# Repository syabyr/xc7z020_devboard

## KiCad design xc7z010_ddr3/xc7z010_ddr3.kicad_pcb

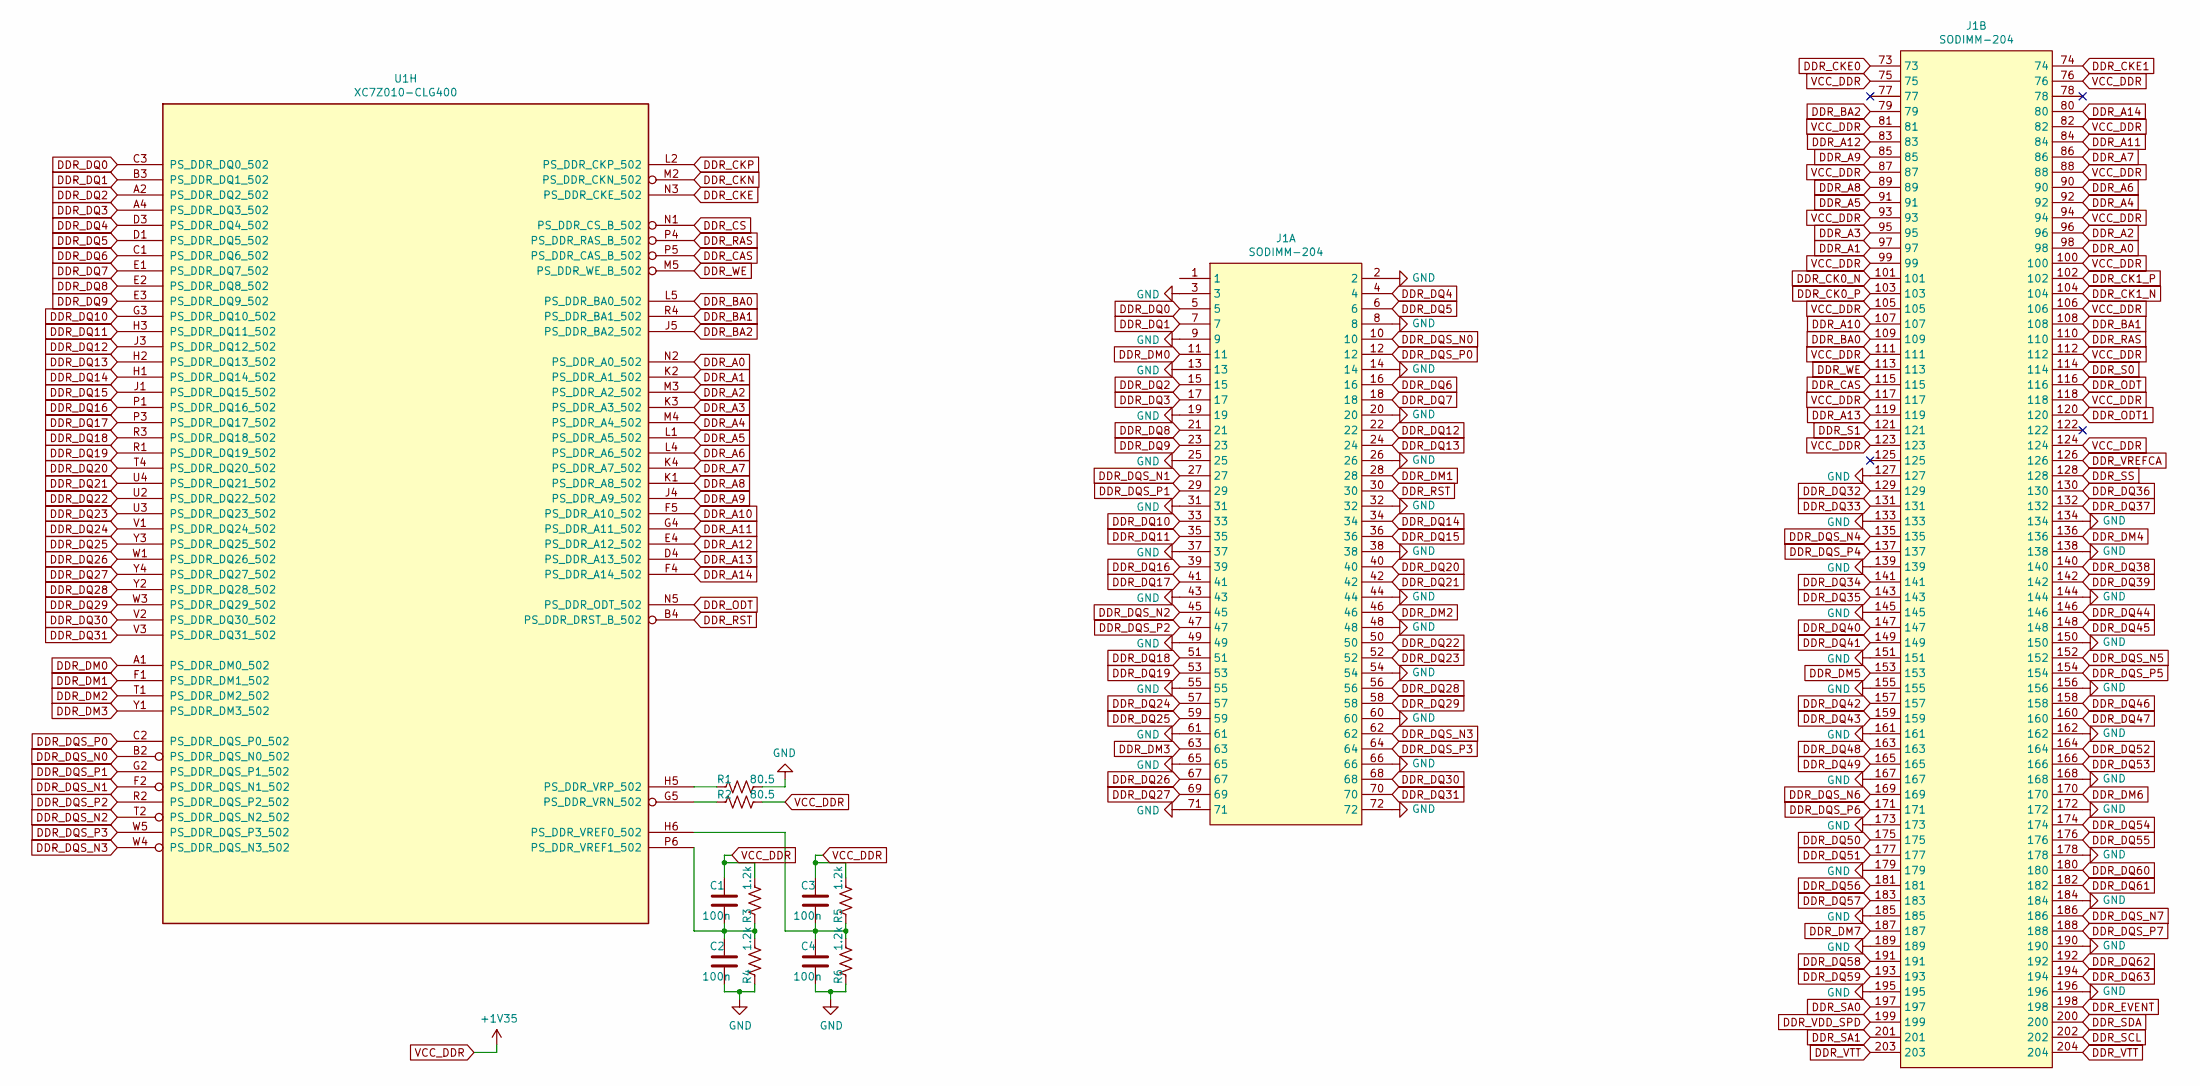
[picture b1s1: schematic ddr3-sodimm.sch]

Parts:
C1, C2, C3, C4: 100n; C_0402_1005Metric
J1: SODIMM-204; Socket_SODIMM_DDR3_TE_2013289_Debug
R1, R2: 80.5; R_0402_1005Metric
R3, R4, R5, R6: 1.2k; R_0402_1005Metric
U1: XC7Z010-CLG400; CLG400-0.8

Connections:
DDR_A0: J1.98, U1.N2 (PS_DDR_A0_502)
DDR_A1: J1.97, U1.K2 (PS_DDR_A1_502)
DDR_A2: J1.96, U1.M3 (PS_DDR_A2_502)
DDR_A3: J1.95, U1.K3 (PS_DDR_A3_502)
DDR_A4: J1.92, U1.M4 (PS_DDR_A4_502)
DDR_A5: J1.91, U1.L1 (PS_DDR_A5_502)
DDR_A6: J1.90, U1.L4 (PS_DDR_A6_502)
DDR_A7: J1.86, U1.K4 (PS_DDR_A7_502)
DDR_A8: J1.89, U1.K1 (PS_DDR_A8_502)
DDR_A9: J1.85, U1.J4 (PS_DDR_A9_502)
DDR_A10: J1.107, U1.F5 (PS_DDR_A10_502)
DDR_A11: J1.84, U1.G4 (PS_DDR_A11_502)
DDR_A12: J1.83, U1.E4 (PS_DDR_A12_502)
DDR_A13: J1.119, U1.D4 (PS_DDR_A13_502)
DDR_A14: J1.80, U1.F4 (PS_DDR_A14_502)
DDR_BA0: J1.109, U1.L5 (PS_DDR_BA0_502)
DDR_BA1: J1.108, U1.R4 (PS_DDR_BA1_502)
DDR_BA2: J1.79, U1.J5 (PS_DDR_BA2_502)
DDR_CAS: J1.115, U1.P5 (PS_DDR_CAS_B_502)
DDR_CK0_N: J1.101
DDR_CK0_P: J1.103
DDR_CK1_N: J1.104
DDR_CK1_P: J1.102
DDR_CKE: U1.N3 (PS_DDR_CKE_502)
DDR_CKE0: J1.73
DDR_CKE1: J1.74
DDR_CKN: U1.M2 (PS_DDR_CKN_502)
DDR_CKP: U1.L2 (PS_DDR_CKP_502)
DDR_CS: U1.N1 (PS_DDR_CS_B_502)
DDR_DM0: J1.11, U1.A1 (PS_DDR_DM0_502)
DDR_DM1: J1.28, U1.F1 (PS_DDR_DM1_502)
DDR_DM2: J1.46, U1.T1 (PS_DDR_DM2_502)
DDR_DM3: J1.63, U1.Y1 (PS_DDR_DM3_502)
DDR_DM4: J1.136
DDR_DM5: J1.153
DDR_DM6: J1.170
DDR_DM7: J1.187
DDR_DQ0: J1.5, U1.C3 (PS_DDR_DQ0_502)
DDR_DQ1: J1.7, U1.B3 (PS_DDR_DQ1_502)
DDR_DQ2: J1.15, U1.A2 (PS_DDR_DQ2_502)
DDR_DQ3: J1.17, U1.A4 (PS_DDR_DQ3_502)
DDR_DQ4: J1.4, U1.D3 (PS_DDR_DQ4_502)
DDR_DQ5: J1.6, U1.D1 (PS_DDR_DQ5_502)
DDR_DQ6: J1.16, U1.C1 (PS_DDR_DQ6_502)
DDR_DQ7: J1.18, U1.E1 (PS_DDR_DQ7_502)
DDR_DQ8: J1.21, U1.E2 (PS_DDR_DQ8_502)
DDR_DQ9: J1.23, U1.E3 (PS_DDR_DQ9_502)
DDR_DQ10: J1.33, U1.G3 (PS_DDR_DQ10_502)
DDR_DQ11: J1.35, U1.H3 (PS_DDR_DQ11_502)
DDR_DQ12: J1.22, U1.J3 (PS_DDR_DQ12_502)
DDR_DQ13: J1.24, U1.H2 (PS_DDR_DQ13_502)
DDR_DQ14: J1.34, U1.H1 (PS_DDR_DQ14_502)
DDR_DQ15: J1.36, U1.J1 (PS_DDR_DQ15_502)
DDR_DQ16: J1.39, U1.P1 (PS_DDR_DQ16_502)
DDR_DQ17: J1.41, U1.P3 (PS_DDR_DQ17_502)
DDR_DQ18: J1.51, U1.R3 (PS_DDR_DQ18_502)
DDR_DQ19: J1.53, U1.R1 (PS_DDR_DQ19_502)
DDR_DQ20: J1.40, U1.T4 (PS_DDR_DQ20_502)
DDR_DQ21: J1.42, U1.U4 (PS_DDR_DQ21_502)
DDR_DQ22: J1.50, U1.U2 (PS_DDR_DQ22_502)
DDR_DQ23: J1.52, U1.U3 (PS_DDR_DQ23_502)
DDR_DQ24: J1.57, U1.V1 (PS_DDR_DQ24_502)
DDR_DQ25: J1.59, U1.Y3 (PS_DDR_DQ25_502)
DDR_DQ26: J1.67, U1.W1 (PS_DDR_DQ26_502)
DDR_DQ27: J1.69, U1.Y4 (PS_DDR_DQ27_502)
DDR_DQ28: J1.56, U1.Y2 (PS_DDR_DQ28_502)
DDR_DQ29: J1.58, U1.W3 (PS_DDR_DQ29_502)
DDR_DQ30: J1.68, U1.V2 (PS_DDR_DQ30_502)
DDR_DQ31: J1.70, U1.V3 (PS_DDR_DQ31_502)
DDR_DQ32: J1.129
DDR_DQ33: J1.131
DDR_DQ34: J1.141
DDR_DQ35: J1.143
DDR_DQ36: J1.130
DDR_DQ37: J1.132
DDR_DQ38: J1.140
DDR_DQ39: J1.142
DDR_DQ40: J1.147
DDR_DQ41: J1.149
DDR_DQ42: J1.157
DDR_DQ43: J1.159
DDR_DQ44: J1.146
DDR_DQ45: J1.148
DDR_DQ46: J1.158
DDR_DQ47: J1.160
DDR_DQ48: J1.163
DDR_DQ49: J1.165
DDR_DQ50: J1.175
DDR_DQ51: J1.177
DDR_DQ52: J1.164
DDR_DQ53: J1.166
DDR_DQ54: J1.174
DDR_DQ55: J1.176
DDR_DQ56: J1.181
DDR_DQ57: J1.183
DDR_DQ58: J1.191
DDR_DQ59: J1.193
DDR_DQ60: J1.180
DDR_DQ61: J1.182
DDR_DQ62: J1.192
DDR_DQ63: J1.194
DDR_DQS_N0: J1.10, U1.B2 (PS_DDR_DQS_N0_502)
DDR_DQS_N1: J1.27, U1.F2 (PS_DDR_DQS_N1_502)
DDR_DQS_N2: J1.45, U1.T2 (PS_DDR_DQS_N2_502)
DDR_DQS_N3: J1.62, U1.W4 (PS_DDR_DQS_N3_502)
DDR_DQS_N4: J1.135
DDR_DQS_N5: J1.152
DDR_DQS_N6: J1.169
DDR_DQS_N7: J1.186
DDR_DQS_P0: J1.12, U1.C2 (PS_DDR_DQS_P0_502)
DDR_DQS_P1: J1.29, U1.G2 (PS_DDR_DQS_P1_502)
DDR_DQS_P2: J1.47, U1.R2 (PS_DDR_DQS_P2_502)
DDR_DQS_P3: J1.64, U1.W5 (PS_DDR_DQS_P3_502)
DDR_DQS_P4: J1.137
DDR_DQS_P5: J1.154
DDR_DQS_P6: J1.171
DDR_DQS_P7: J1.188
DDR_EVENT: J1.198
DDR_ODT: J1.116, U1.N5 (PS_DDR_ODT_502)
DDR_ODT1: J1.120
DDR_RAS: J1.110, U1.P4 (PS_DDR_RAS_B_502)
DDR_RST: J1.30, U1.B4 (PS_DDR_DRST_B_502)
DDR_S0: J1.114
DDR_S1: J1.121
DDR_SA0: J1.197
DDR_SA1: J1.201
DDR_SCL: J1.202
DDR_SDA: J1.200
DDR_SS: J1.128
DDR_VDD_SPD: J1.199
DDR_VREFCA: J1.126
DDR_VTT: J1.203, J1.204
DDR_WE: J1.113, U1.M5 (PS_DDR_WE_B_502)
GND: C2.1, C4.1, J1.2, J1.3, J1.8, J1.9, J1.13, J1.14, J1.19, J1.20, J1.25, J1.26, J1.31, J1.32, J1.37, J1.38, J1.43, J1.44, J1.48, J1.49, J1.54, J1.55, J1.60, J1.61, J1.65, J1.66, J1.71, J1.72, J1.127, J1.133, J1.134, J1.138, J1.139, J1.144, J1.145, J1.150, J1.151, J1.155, J1.156, J1.161, J1.162, J1.167, J1.168, J1.172, J1.173, J1.178, J1.179, J1.184, J1.185, J1.189, J1.190, J1.195, J1.196, R1.1, R4.2, R6.2
unnamed: C1.1, C2.2, R3.2, R4.1, U1.P6 (PS_DDR_VREF1_502)
unnamed: C3.1, C4.2, R5.2, R6.1, U1.H6 (PS_DDR_VREF0_502)
unnamed: R1.2, U1.H5 (PS_DDR_VRP_502)
unnamed: R2.2, U1.G5 (PS_DDR_VRN_502)
VCC_DDR: C1.2, C3.2, J1.75, J1.76, J1.81, J1.82, J1.87, J1.88, J1.93, J1.94, J1.99, J1.100, J1.105, J1.106, J1.111, J1.112, J1.117, J1.118, J1.123, J1.124, R2.1, R3.1, R5.1

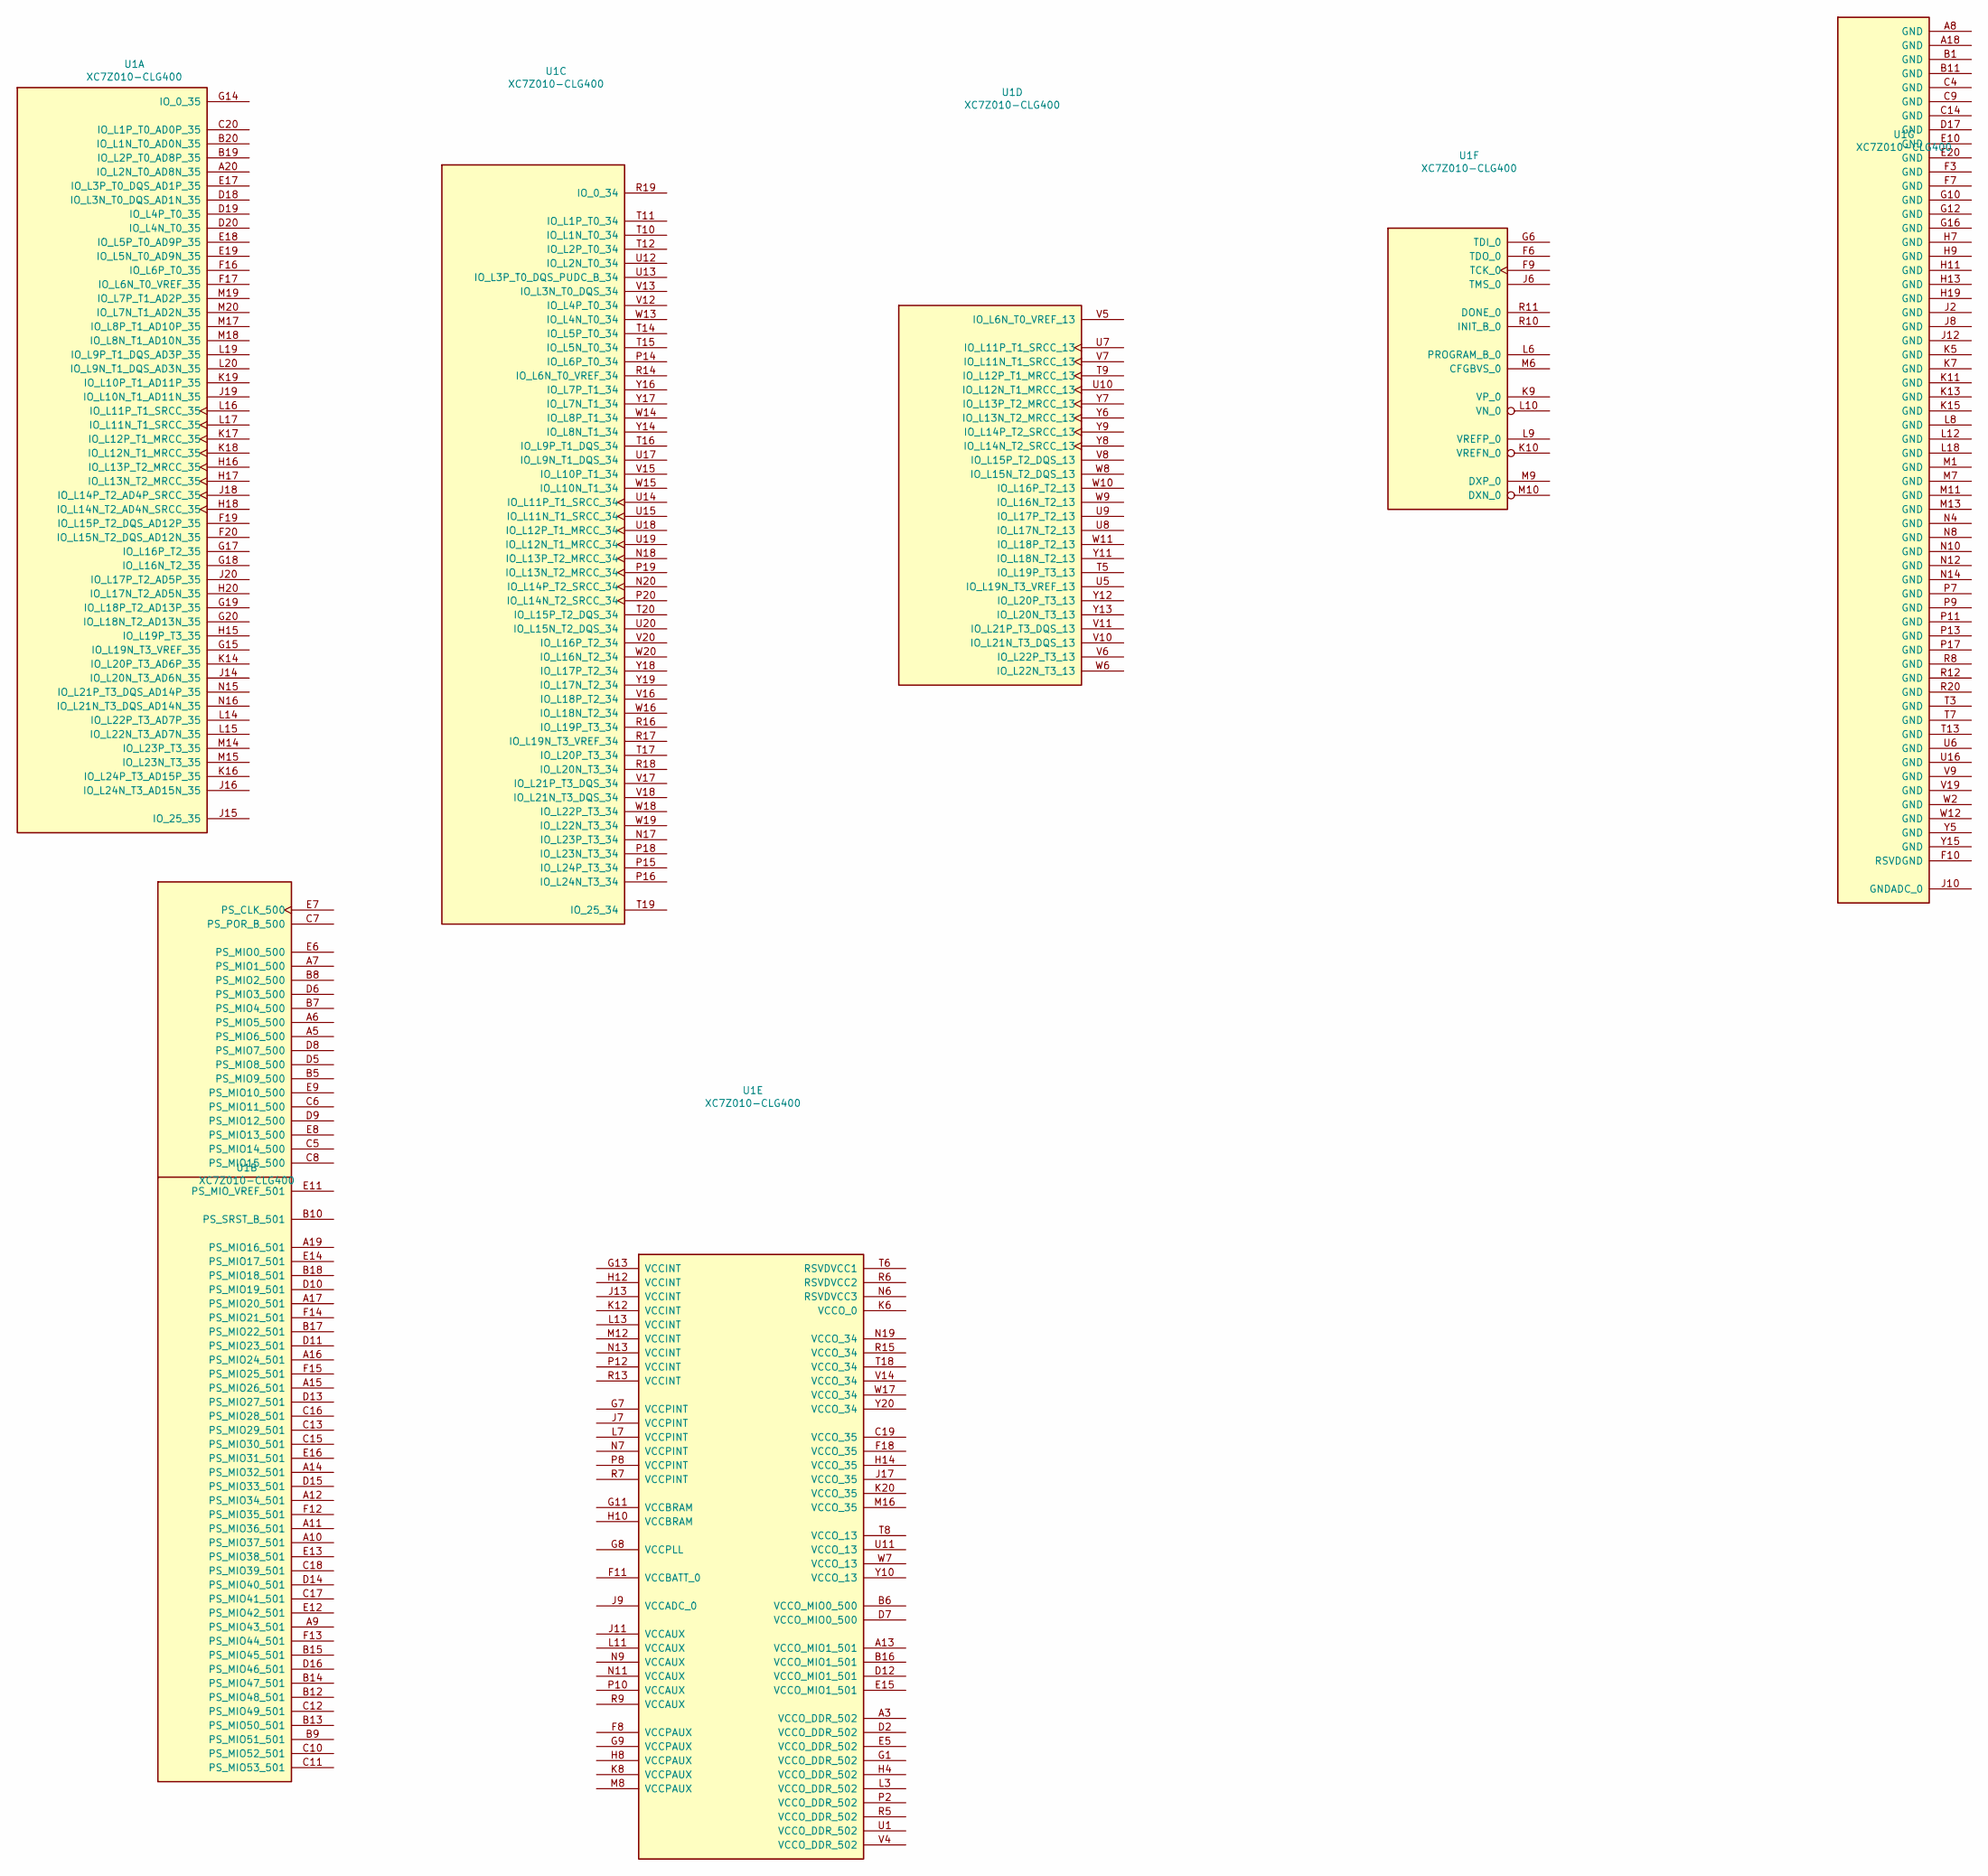
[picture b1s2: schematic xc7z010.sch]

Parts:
U1: XC7Z010-CLG400; CLG400-0.8

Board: 2 copper layers, 12 parts (0 on the bottom side), 74 nets, no tracks yet.

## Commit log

2021-02-23 init
2021-02-23 202101212
